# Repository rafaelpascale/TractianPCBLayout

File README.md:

TRACTIAN CHALLENGE
The microcontroller that is being used is the ESP32 from heltec which already has the BLE, Lora and OLED integrated into it, the ESP 32 power supply is from 4.5 to 12V, so a voltage regulator for 5VDC was also placed a battery module to charge the 18650maH battery which is located in the lower corner of the board. There are also 2 connectors to fit the temperature and humidity sensor (DHT22) so that it can be placed on the outside of the case and an i2c extension to connect the OLED or LCD display.

DESAFIO TRACTIAN 
O microcontrador que está sendo usado é o ESP32 da heltec que ja tem o BLE, Lora e OLED integrados nele, a alimetação do ESP 32 é de 4,5 a 12V, por isso foi colocado um regulador de tensao para 5VDC, também foi colocado um modulo de bateria para carregar a bateria de 18650maH que está alocado no canto inferior da placa. Há também 2 conectores para encaixar o sensor de temperatura e umidade( DHT22) para que seja colocado na parte externa do gabinete e uma extensão do i2c para ligar o display OLED ou LCD

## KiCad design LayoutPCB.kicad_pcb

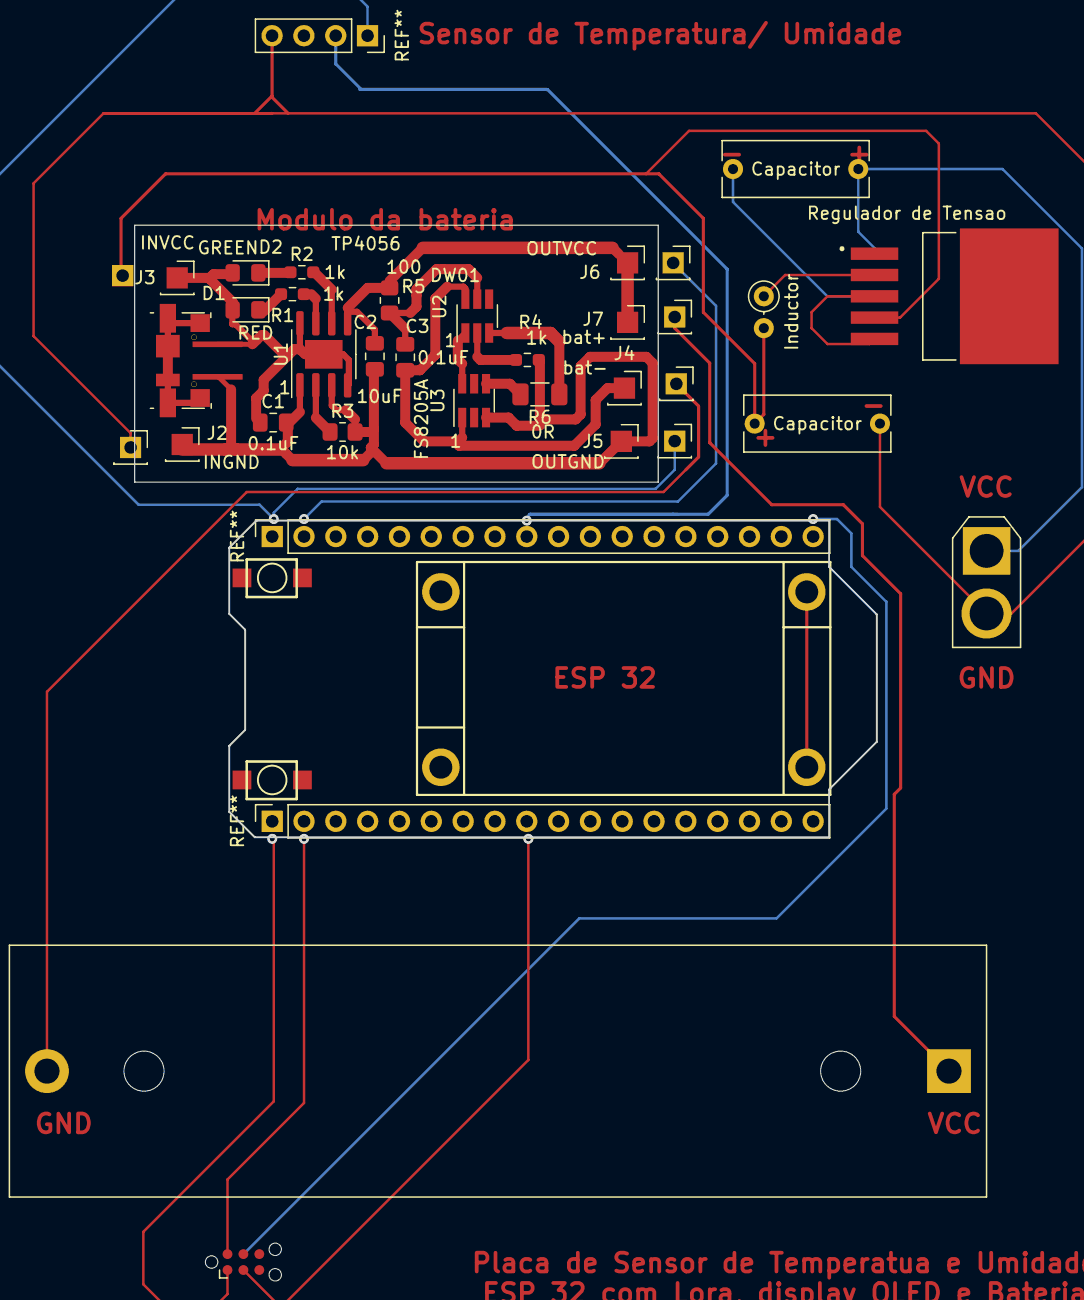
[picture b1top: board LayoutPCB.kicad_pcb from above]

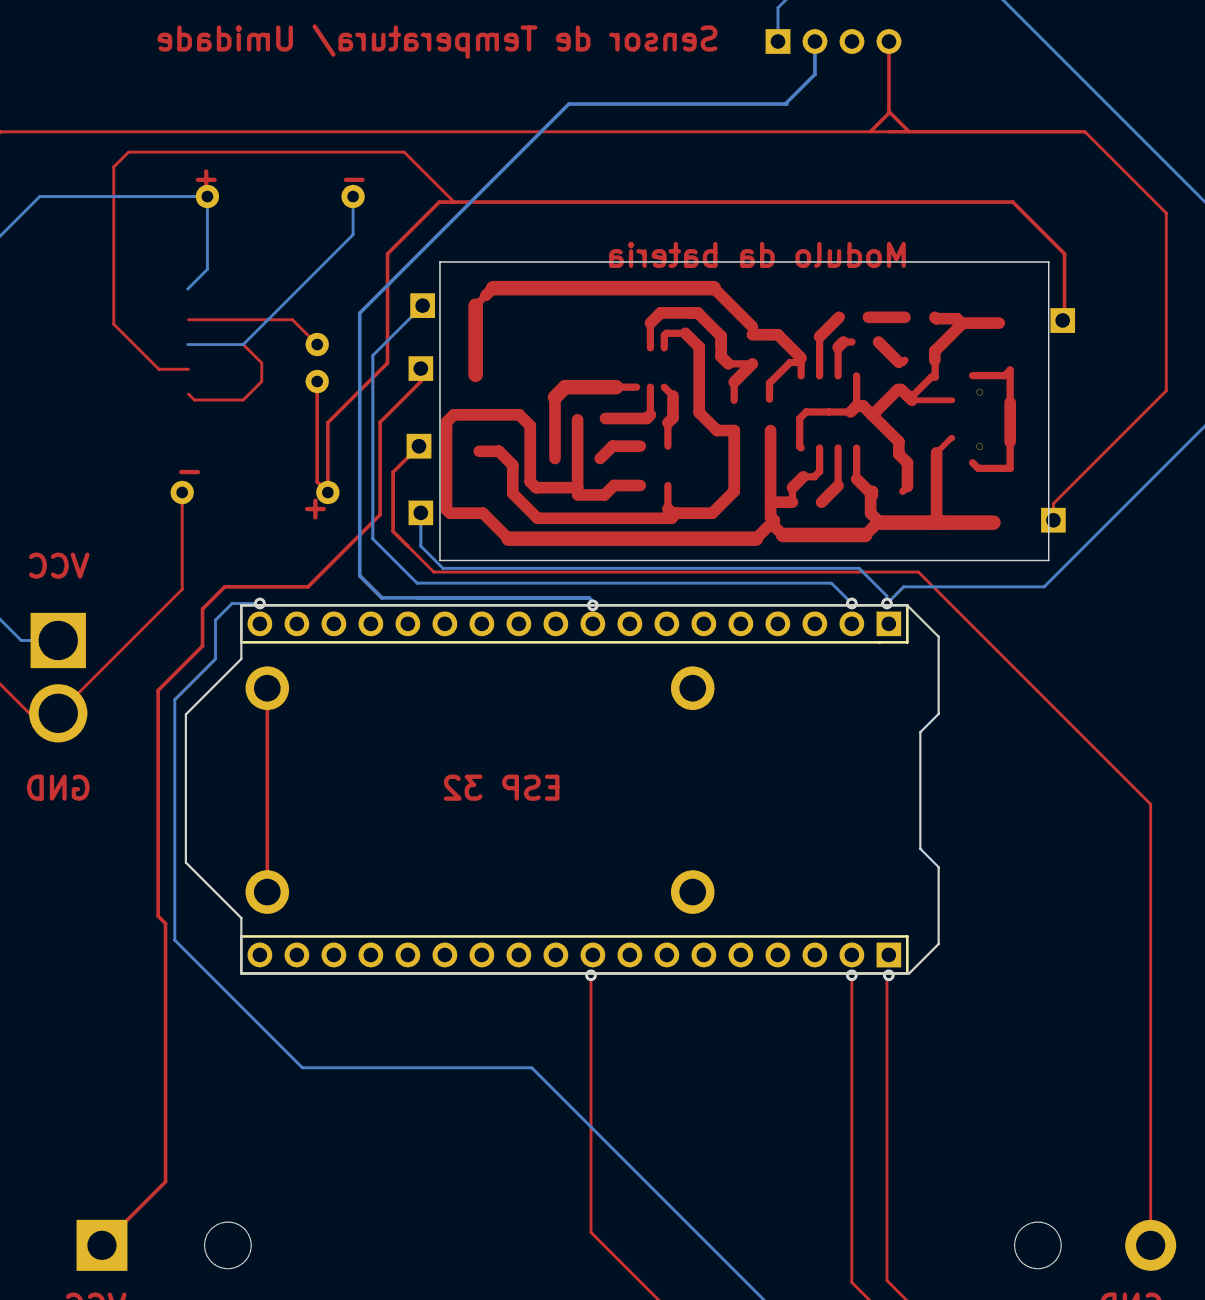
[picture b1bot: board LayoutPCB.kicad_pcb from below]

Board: 2 copper layers, 59.2 x 48.9 mm, 29 parts (2 on the bottom side), 14 nets.

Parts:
C1, C3: 0.1uF; C_0805_2012Metric_Pad1.18x1.45mm_HandSolder
C2: 10uF; C_0805_2012Metric_Pad1.18x1.45mm_HandSolder
Capacitor : 220nF; C_Rect_L11.5mm_W4.3mm_P10.00mm_MKT
Capacitor #2: 680nF; C_Rect_L11.5mm_W4.3mm_P10.00mm_MKT
D1: RED; LED_0805_2012Metric_Pad1.15x1.40mm_HandSolder
D2: GREEN; LED_0805_2012Metric_Pad1.15x1.40mm_HandSolder
Inductor: 33uF; L_Axial_L5.3mm_D2.2mm_P2.54mm_Vertical_Vishay_IM-1
J1: USB_B_Micro; tp4056_USB_Micro-B_Molex_47346-0001_fix
J2, J3, J4, J5, J6, J7: Conn_01x01_Female; PinSocket_1x01_P2.54mm_Vertical
JP2, JP3: Header 18; HDR1X18_1
R1, R2, R4: 1k; R_0603_1608Metric_Pad0.98x0.95mm_HandSolder
R3: 10k; R_0805_2012Metric_Pad1.20x1.40mm_HandSolder
R5: 100; R_0805_2012Metric_Pad1.20x1.40mm_HandSolder
R6: 0R; R_1206_3216Metric_Pad1.30x1.75mm_HandSolder
Regulador de Tensao : LM2596S-5; TO170P1524X483-6N
S1: RESET; TACK_SWITCH_3X4X2_1
S2: BTN-0; TACK_SWITCH_3X4X2_1
U1: TP4056; SOIC-8-1EP_3.9x4.9mm_P1.27mm_EP2.29x3mm
U2: DW01; SOT-23-6_Handsoldering
U3: FS8205A; SOT-23-6_Handsoldering

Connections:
/G1: U2.1 (OD), U3.6 (G1)
/G2: R6.2, U3.4 (G2)
/OC: R6.1, U2.3 (OC)
BAT+: C2.1, J6.1, J7.1, R5.1, U1.5 (BAT)
BAT-: C3.2, J4.1, U2.6 (GND), U3.1 (S1)
GND: C1.2, C2.2, J1.5 (GND), J2.1, J5.1, R3.2, R4.1, U1.1 (TEMP), U1.3 (GND), U3.3 (S2)
unnamed: C3.1, R5.2, U2.5 (VCC)
unnamed: D1.1 (K), R1.1
unnamed: D2.1 (K), R2.1
unnamed: R1.2, U1.7 (~CHRG)
unnamed: R2.2, U1.6 (~STDBY)
unnamed: R3.1, U1.2 (PROG)
unnamed: R4.2, U2.2 (CS)
VIN: C1.1, D1.2 (A), D2.2 (A), J1.1 (VBUS), J3.1, U1.4 (VCC), U1.8 (CE), U1.9 (PP)

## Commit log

2022-04-05 Colocando os componentes
2022-04-05 Acrescentando Componentes
2022-04-06 Colocando mais componentes
2022-04-06 Gerando os arquivos
2022-04-06 Colocando Nomes
2022-04-06 Mais descrição
2022-04-06 Atualizando os arquivos
2022-04-07 Adicionando os conectores
2022-04-10 Impressao da PCB
